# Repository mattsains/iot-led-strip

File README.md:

# IoT LED strip controller
An open source hardware implementation of a IoT controller for LED strips.

This board is based on an ESP32-WROOM module and can control 2 RGB(W) and one Neopixel-like strip with a supply between 5V and 24V. Each channel can sink up to 3.4A continuous through the DMN3404L driver MOSFETs.

The ESP32 allows IoT applications over the Internet (eg., Alexa, Google Home, etc) as well as over Bluetooth (eg., P2P mobile app). The ESP32 is powered through an on-board switch-mode power supply that works over the LED input voltage range of 5V to 24V.

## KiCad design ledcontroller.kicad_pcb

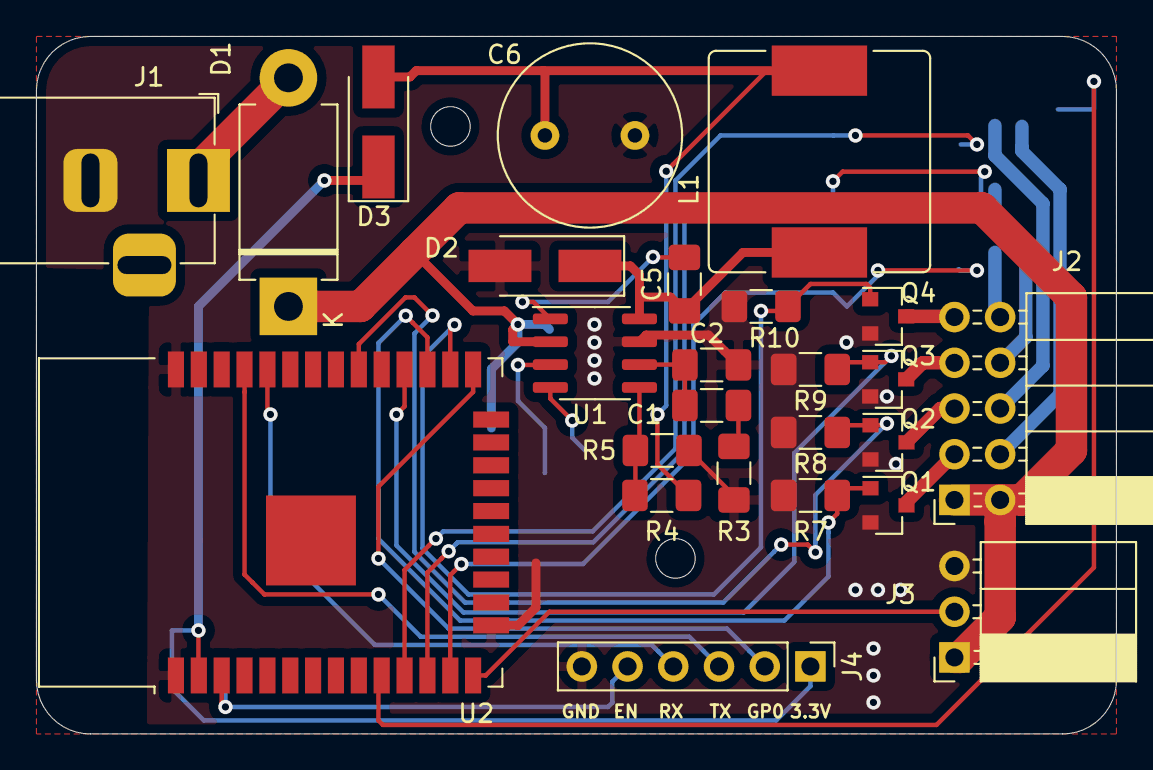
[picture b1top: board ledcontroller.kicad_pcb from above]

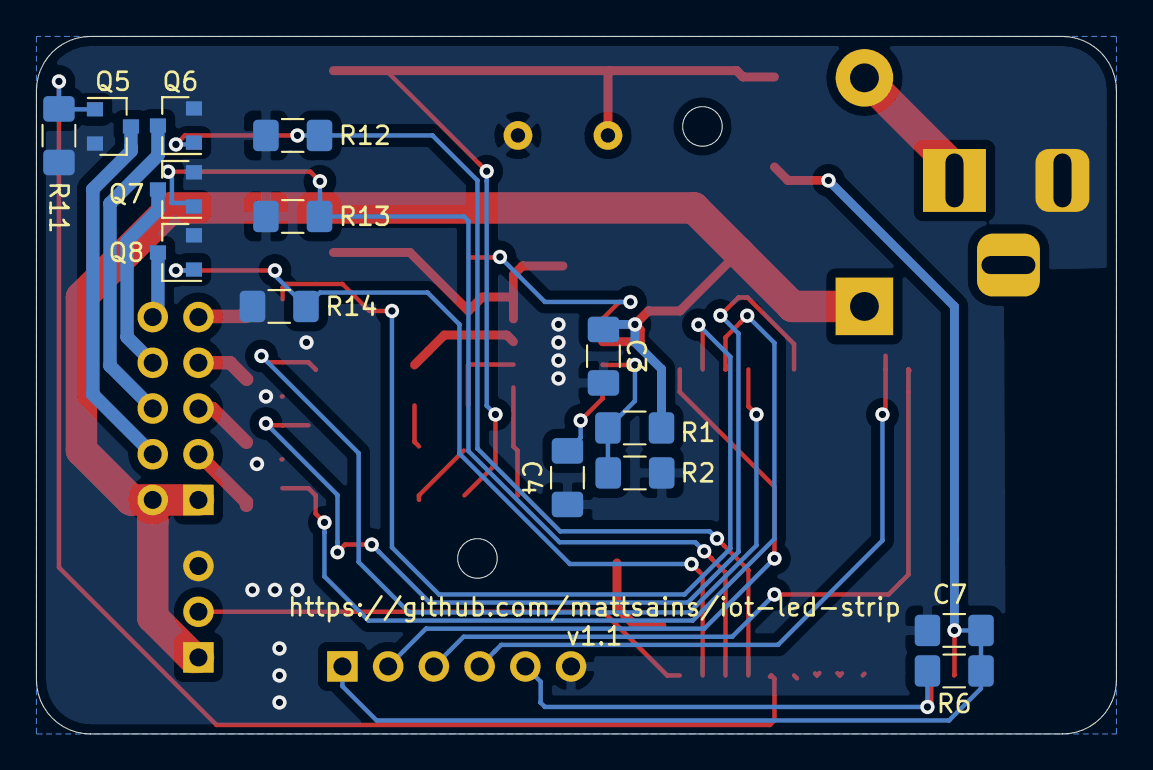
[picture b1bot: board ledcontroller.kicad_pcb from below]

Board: 2 copper layers, 60.0 x 38.8 mm, 41 parts (14 on the bottom side), 33 nets.

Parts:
 : MountingHole_2.2mm_M2
 #2: MountingHole_2.2mm_M2
C1, C2: 220pF; C_1206_3216Metric_Pad1.42x1.75mm_HandSolder
C3, C5, C7: 0.1uF; C_1206_3216Metric_Pad1.42x1.75mm_HandSolder
C4: 0.015uF; C_1206_3216Metric_Pad1.42x1.75mm_HandSolder
C6: 470uF; C_Radial_D10.0mm_H16.0mm_P5.00mm
D1: SB2060; D_DO-201AD_P12.70mm_Horizontal
D2, D3: B240A; D_SMA_Handsoldering
J1: Barrel_Jack; BarrelJack_Horizontal
J2: RGBW analog; PinSocket_2x05_P2.54mm_Horizontal
J3: RGB addressable; PinSocket_1x03_P2.54mm_Horizontal
J4: Conn_01x06_Male; PinHeader_1x06_P2.54mm_Vertical
L1: 47uH; L_Bourns_SRR1210A
Q1, Q2, Q3, Q4, Q5, Q6, Q7, Q8: DMN3404L; SOT-23
R1: 233k; R_1206_3216Metric_Pad1.42x1.75mm_HandSolder
R2: 312k; R_1206_3216Metric_Pad1.42x1.75mm_HandSolder
R3: 30.9k; R_1206_3216Metric_Pad1.42x1.75mm_HandSolder
R4: 10.2k; R_1206_3216Metric_Pad1.42x1.75mm_HandSolder
R5: 3.24k; R_1206_3216Metric_Pad1.42x1.75mm_HandSolder
R6, R7, R8, R9, R10, R11, R12, R13, R14: 20k; R_1206_3216Metric_Pad1.42x1.75mm_HandSolder
U1: TPS54233; SOIC-8_3.9x4.9mm_P1.27mm
U2: ESP32-WROOM-32

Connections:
+3V3: C7.1, D3.1, J4.1, R6.1, U2.2
/B1: Q3.1, R9.2, U2.28
/B2: Q7.1, R13.2, U2.12
/DAT: J3.2, U2.14
/EN: J4.5, R6.2, U2.3
/G1: Q1.1, R7.2, U2.27
/G2: Q5.1, R11.2, U2.10
/R1: Q2.1, R8.2, U2.30
/R2: Q6.1, R12.2, U2.11
/W1: Q4.1, R10.2, U2.26
/W2: Q8.1, R14.2, U2.13
GND: C2.2, C3.2, C4.2, C6.2, C7.2, D2.2, J1.2, J3.3, J4.6, Q1.2, Q2.2, Q3.2, Q4.2, Q5.2, Q6.2, Q7.2, Q8.2, R2.2, R3.2, R5.2, R7.1, R8.1, R9.1, R10.1, R11.1, R12.1, R13.1, R14.1, U1.7, U2.1, U2.15, U2.38
unnamed: C1.1, C2.1, U1.6
unnamed: C1.2, R3.1
unnamed: C4.1, U1.4
unnamed: C5.1, D2.1, L1.1, U1.8
unnamed: C5.2, U1.1
unnamed: C6.1, D3.2, L1.2, R4.1
unnamed: D1.2, J1.1
unnamed: J2.3, Q1.3
unnamed: J2.4, Q5.3
unnamed: J2.5, Q2.3
unnamed: J2.6, Q6.3
unnamed: J2.7, Q3.3
unnamed: J2.8, Q7.3
unnamed: J2.9, Q4.3
unnamed: J2.10, Q8.3
unnamed: J4.2, U2.25
unnamed: J4.3, U2.35
unnamed: J4.4, U2.34
unnamed: R1.2, R2.1, U1.3
unnamed: R4.2, R5.1, U1.5
VPP: C3.1, D1.1, J2.1, J2.2, J3.1, R1.1, U1.2

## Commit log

2020-03-12 Initial design done
2020-03-12 Added exports directory
2020-03-14 Increase track width for power; release v1
2020-03-28 fixes #4 #3 #2
2020-03-29 respin for v1.1
2020-03-29 added firmware project
2020-04-19 WiFi control and simple JS server
2020-04-19 Change to use websockets
2020-04-27 Refactor firmware and fix server bug
2020-04-27 Move wifi password to nvm
2020-04-27 refactor into header files
2020-04-28 Add OOB AP
2020-04-29 Complete basic setup workflow
2020-05-01 Move circuit design to subdirectory
2020-05-03 wip: firmware
2020-05-05 Write draft of addressable strip control, and fix https implementation
2021-05-30 Bump ws from 7.2.3 to 7.4.6 in /server
    Bumps [ws](https://github.com/websockets/ws) from 7.2.3 to 7.4.6.
    - [Release notes](https://github.com/websockets/ws/releases)
    - [Commits](https://github.com/websockets/ws/compare/7.2.3...7.4.6)
2022-12-07 Bump qs and express in /server
    Bumps [qs](https://github.com/ljharb/qs) to 6.11.0 and updates ancestor dependency [express](https://github.com/expressjs/express). These dependencies need to be updated together.
    Updates `qs` from 6.7.0 to 6.11.0
    - [Release notes](https://github.com/ljharb/qs/releases)
    - [Changelog](https://github.com/ljharb/qs/blob/main/CHANGELOG.md)
    - [Commits](https://github.com/ljharb/qs/compare/v6.7.0...v6.11.0)
    Updates `express` from 4.17.1 to 4.18.2
2024-03-28 Bump express from 4.18.2 to 4.19.2 in /server
    Bumps [express](https://github.com/expressjs/express) from 4.18.2 to 4.19.2.
    - [Release notes](https://github.com/expressjs/express/releases)
    - [Changelog](https://github.com/expressjs/express/blob/master/History.md)
    - [Commits](https://github.com/expressjs/express/compare/4.18.2...4.19.2)
    ---
    updated-dependencies:
2024-04-15 Bump ws from 5.2.2 to 7.5.9 in /server
    Bumps [ws](https://github.com/websockets/ws) from 5.2.2 to 7.5.9.
    - [Release notes](https://github.com/websockets/ws/releases)
    - [Commits](https://github.com/websockets/ws/compare/5.2.2...7.5.9)
    ---
    updated-dependencies:
    - dependency-name: ws
2024-06-18 Bump ws from 7.4.6 to 7.5.10 in /server
    Bumps [ws](https://github.com/websockets/ws) from 7.4.6 to 7.5.10.
    - [Release notes](https://github.com/websockets/ws/releases)
    - [Commits](https://github.com/websockets/ws/compare/7.4.6...7.5.10)
    ---
    updated-dependencies:
    - dependency-name: ws
2024-09-10 Bump path-to-regexp and express in /server
    Bumps [path-to-regexp](https://github.com/pillarjs/path-to-regexp) to 0.1.10 and updates ancestor dependency [express](https://github.com/expressjs/express). These dependencies need to be updated tog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
    Updates `path-to-regexp` from 0.1.7 to 0.1.10
    - [Release notes](https://github.com/pillarjs/path-to-regexp/releases)
    - [Changelog](https://github.com/pillarjs/path-to-regexp/blob/master/History.md)
    - [Commits](https://github.com/pillarjs/path-to-regexp/compare/v0.1.7...v0.1.10)
    Updates `express` from 4.19.2 to 4.20.0
2024-09-18 Bump serve-static and express in /server
    Bumps [serve-static](https://github.com/expressjs/serve-static) to 1.16.2 and updates ancestor dependency [express](https://github.com/expressjs/express). These dependencies need to be updated togeth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
    Updates `serve-static` from 1.15.0 to 1.16.2
    - [Release notes](https://github.com/expressjs/serve-static/releases)
    - [Changelog](https://github.com/expressjs/serve-static/blob/v1.16.2/HISTORY.md)
    - [Commits](https://github.com/expressjs/serve-static/compare/v1.15.0...v1.16.2)
    Updates `express` from 4.19.2 to 4.21.0
2024-09-18 Bump send and express in /server
    Bumps [send](https://github.com/pillarjs/send) to 0.19.0 and updates ancestor dependency [express](https://github.com/expressjs/express). These dependencies need to be updated together.
    Updates `send` from 0.18.0 to 0.19.0
    - [Release notes](https://github.com/pillarjs/send/releases)
    - [Changelog](https://github.com/pillarjs/send/blob/master/HISTORY.md)
    - [Commits](https://github.com/pillarjs/send/compare/0.18.0...0.19.0)
    Updates `express` from 4.19.2 to 4.21.0
2024-09-21 Bump body-parser and express in /server
    Bumps [body-parser](https://github.com/expressjs/body-parser) to 1.20.3 and updates ancestor dependency [express](https://github.com/expressjs/express). These dependencies need to be updated together.
    Updates `body-parser` from 1.20.2 to 1.20.3
    - [Release notes](https://github.com/expressjs/body-parser/releases)
    - [Changelog](https://github.com/expressjs/body-parser/blob/master/HISTORY.md)
    - [Commits](https://github.com/expressjs/body-parser/compare/1.20.2...1.20.3)
    Updates `express` from 4.19.2 to 4.21.0
2024-10-19 Bump cookie and express in /server
    Bumps [cookie](https://github.com/jshttp/cookie) to 0.7.1 and updates ancestor dependency [express](https://github.com/expressjs/express). These dependencies need to be updated together.
    Updates `cookie` from 0.6.0 to 0.7.1
    - [Release notes](https://github.com/jshttp/cookie/releases)
    - [Commits](https://github.com/jshttp/cookie/compare/v0.6.0...v0.7.1)
    Updates `express` from 4.19.2 to 4.21.1
    - [Release notes](https://github.com/expressjs/express/releases)
2024-12-07 Bump path-to-regexp and express in /server
    Bumps [path-to-regexp](https://github.com/pillarjs/path-to-regexp) to 0.1.12 and updates ancestor dependency [express](https://github.com/expressjs/express). These dependencies need to be updated tog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
    Updates `path-to-regexp` from 0.1.7 to 0.1.12
    - [Release notes](https://github.com/pillarjs/path-to-regexp/releases)
    - [Changelog](https://github.com/pillarjs/path-to-regexp/blob/master/History.md)
    - [Commits](https://github.com/pillarjs/path-to-regexp/compare/v0.1.7...v0.1.12)
    Updates `express` from 4.19.2 to 4.21.2
